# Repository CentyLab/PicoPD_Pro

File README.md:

# PicoPD Pro
Pico PD Pro is a development board for USB Power Delivery development with Raspberry Pi Pico footprint. The board can help you negotiate voltage from USB PD 3.1 with PPS (programable power supply) and AVS (Adjustable Voltage Supply) up to 5A of current at 30V max. The board feature input current/voltage/temperture reading as well as power switch to cut of the current to external devices. The 30V voltage limit is the max input voltage of the AP33772S IC.

# Quick links
[AP33772S Cpp Library](https://github.com/CentyLab/AP33772S-Cpp)

[AP33772S CircuitPython Library](https://github.com/hansendc/CircuitPython_AP33772s/) -> Big thanks to [@hansendc](https://github.com/hansendc)

[PicoPD Pro Pinout](#picopd-pro-pinout)

[Setup for AP33772S objects](#setup-for-AP33772S-objects)

[Basic AP33772S functions](#basic-ap33772S-functions)

[Important note](#important-note)

[Arduino IDE setup](#arduino-ide-setup)

[VSCode PlatformIO setup](#vscode-platformio-setup)

[Enable Serial print for debugging](#enable-serial-debug)

# PicoPD Pro Pinout

# Setup for AP33772S objects
To use AP33772 IC with the library, first you need to create a `usbpd` object. Then set up your I2C pins and start collecting the power profiles from your charger. Ensure your delay after `Wire.begin()` is more than 500ms for stable PDOs request. Enable pin 23 to allow VBUS pass-through.
```
AP33772S usbpd; // Automatically wire to Wire0

void setup()
{
  Wire.setSDA(0); // Set the correct SDA0 pin
  Wire.setSCL(1); // Set the correct SCL0 pin
  Wire.begin();
  Serial.begin(115200);
  delay(1000); 		// Delay is needed for the IC to obtain PDOs
  usbpd.begin(); 	// Start pulling the PDOs from power supply

  pinMode(25, OUTPUT); // Built in LED

  usbpd.printPDO(); //Print out PDO to Serial port
  usbpd.setOutput(0); // Turn off output switch
}
```

# Basic AP33772S functions
Common functions are:
```
displayProfiles(); //Print out PDOs in Serial
mapPPSAVSInfo();
setFixPDO(int pdoIndex, int max_current);
setPPSPDO(int pdoIndex, int target_voltage, int max_current);
setAVSPDO(int pdoIndex, int target_voltage, int max_current);
setOutput(uint8_t flag);

readVoltage();      //Return voltage in mV
readCurrent();      //Return current in mA      
readTemp();         //Return temperature in C                          
```

# Important note

Calling `usbpd.displayProfiles()` without `Serial.begin()` can soft-brick your PicoPD. Causing the IC to be non-recognizable by your computer. You will have to use PicoProbe to reflash the chip. Check out @Patronics [PicoProbePCB](https://github.com/Patronics/PicoProbePCB) if you would like to make a stable fixture for firmware debugging.

If you want to use PicoPD Pro as an AP33772S evalulation board with your own micro-controller, flash the board with **AP33772S_Eval.uf2** using the drag and drop method. This firmware will config GP0 and GP1 as INPUT to prevent I2C interferance with your own add on micro-controller like ESP32 or STM32.

# Enable Serial Debug

To enable Serial debug, there are 2 main methods:

**Using USB-C Power/Data splitter (easiest):** Use a USB-C Splitter that separates the USB 2.0 signal into another USB-C port. You only need USB 2.0 FullSpeed (12Mbps) for the job, but never hurts to get extra speed if needed later. 

* [USB-C Power/Data Splitter](https://lectronz.com/products/usb-c-splitter) (USB-HighSpeed)
* [USB-C PD Power Splitter](https://www.tindie.com/products/essenceeng/usb-c-pd-power-splitter/) (USB-HighSpeed)

**Using UART communication**: Make sure you are not using GP0 and GP1 as they are reserved for I2C0 channel for AP33772 IC. Check out Youtube tutorial: [Talk to Your Pico Over Serial](https://www.youtube.com/watch?v=pbWhoJdYA1s)

# Arduino IDE setup
Open Arduino IDE, select File -> Preference

Copy this line below and place in "Aditional Boards Manager URLs" -> OK. This will allow you to pull the Earlephilhower Pico core that work with the AP33772 library.

```
https://github.com/earlephilhower/arduino-pico/releases/download/global/package_rp2040_index.json
```

From Board Manager, search for "Pico" and install the "Raspberry Pi Pico/RP2040" core by Earlephilhower

Now from Tool -> Board -> Raspberry Pi Pico/RP2040 -> Raspberry Pi Pico

Now download the latest AP33772 library as a Zip file

```
https://github.com/CentyLab/AP33772S-Cpp
```

Import the AP33772S library into your Arduino IDE. Sketch -> Include library -> Add .ZIP Library ...

Now you start using the Example code in File -> Examples -> AP33772-Cpp-main. The example is ready to compile and flash on to your PicoPD.

Now you can plug in your USB-C cable with Power Delivery 2.0/3.0/3.1. If you also like to have serial print out, check out [Enable Serial print for debugging](#enable-serial-debug).

# VSCode PlatformIO setup
After [VSCode](https://code.visualstudio.com/) installation, you will need to install PlatformIO extension.

Now create a new PlatformIO project
+ Name:WhatEverYouWantToCallit
+ Board: Pico (RasberryPi)
+ Framework: Arduino (default)

Click "Finish"

In your new project, copy this and replace everything in platformio.ini. This is how you ask PlatformIO to compile using Earlephilhower Pico core, and enable upload via USB.

```
[env:pico]
platform = https://github.com/maxgerhardt/platform-raspberrypi.git
board = pico
framework = arduino
board_build.core = earlephilhower

;; If directly upload from PC
upload_protocol = picotool
```

Now download the latest AP33772 library as a Zip file. Unzip and place the folder in `lib`

```
https://github.com/CentyLab/AP33772S-Cpp
```

Your lib folder should look like this

To try out example code, you copy the content inside `lib/Compiled for PicoPD/PPSCycling/PPSCycling.ino`, And replace everything in your `src/main.cpp`

Now you can plug the PicoPD to your computer via USB-C and hit the upload button. After this, you will have to connect a charger to PicoPD to see the voltage cycling example. If you also like to have serial print out, check out [Enable Serial print for debugging](#enable-serial-debug).

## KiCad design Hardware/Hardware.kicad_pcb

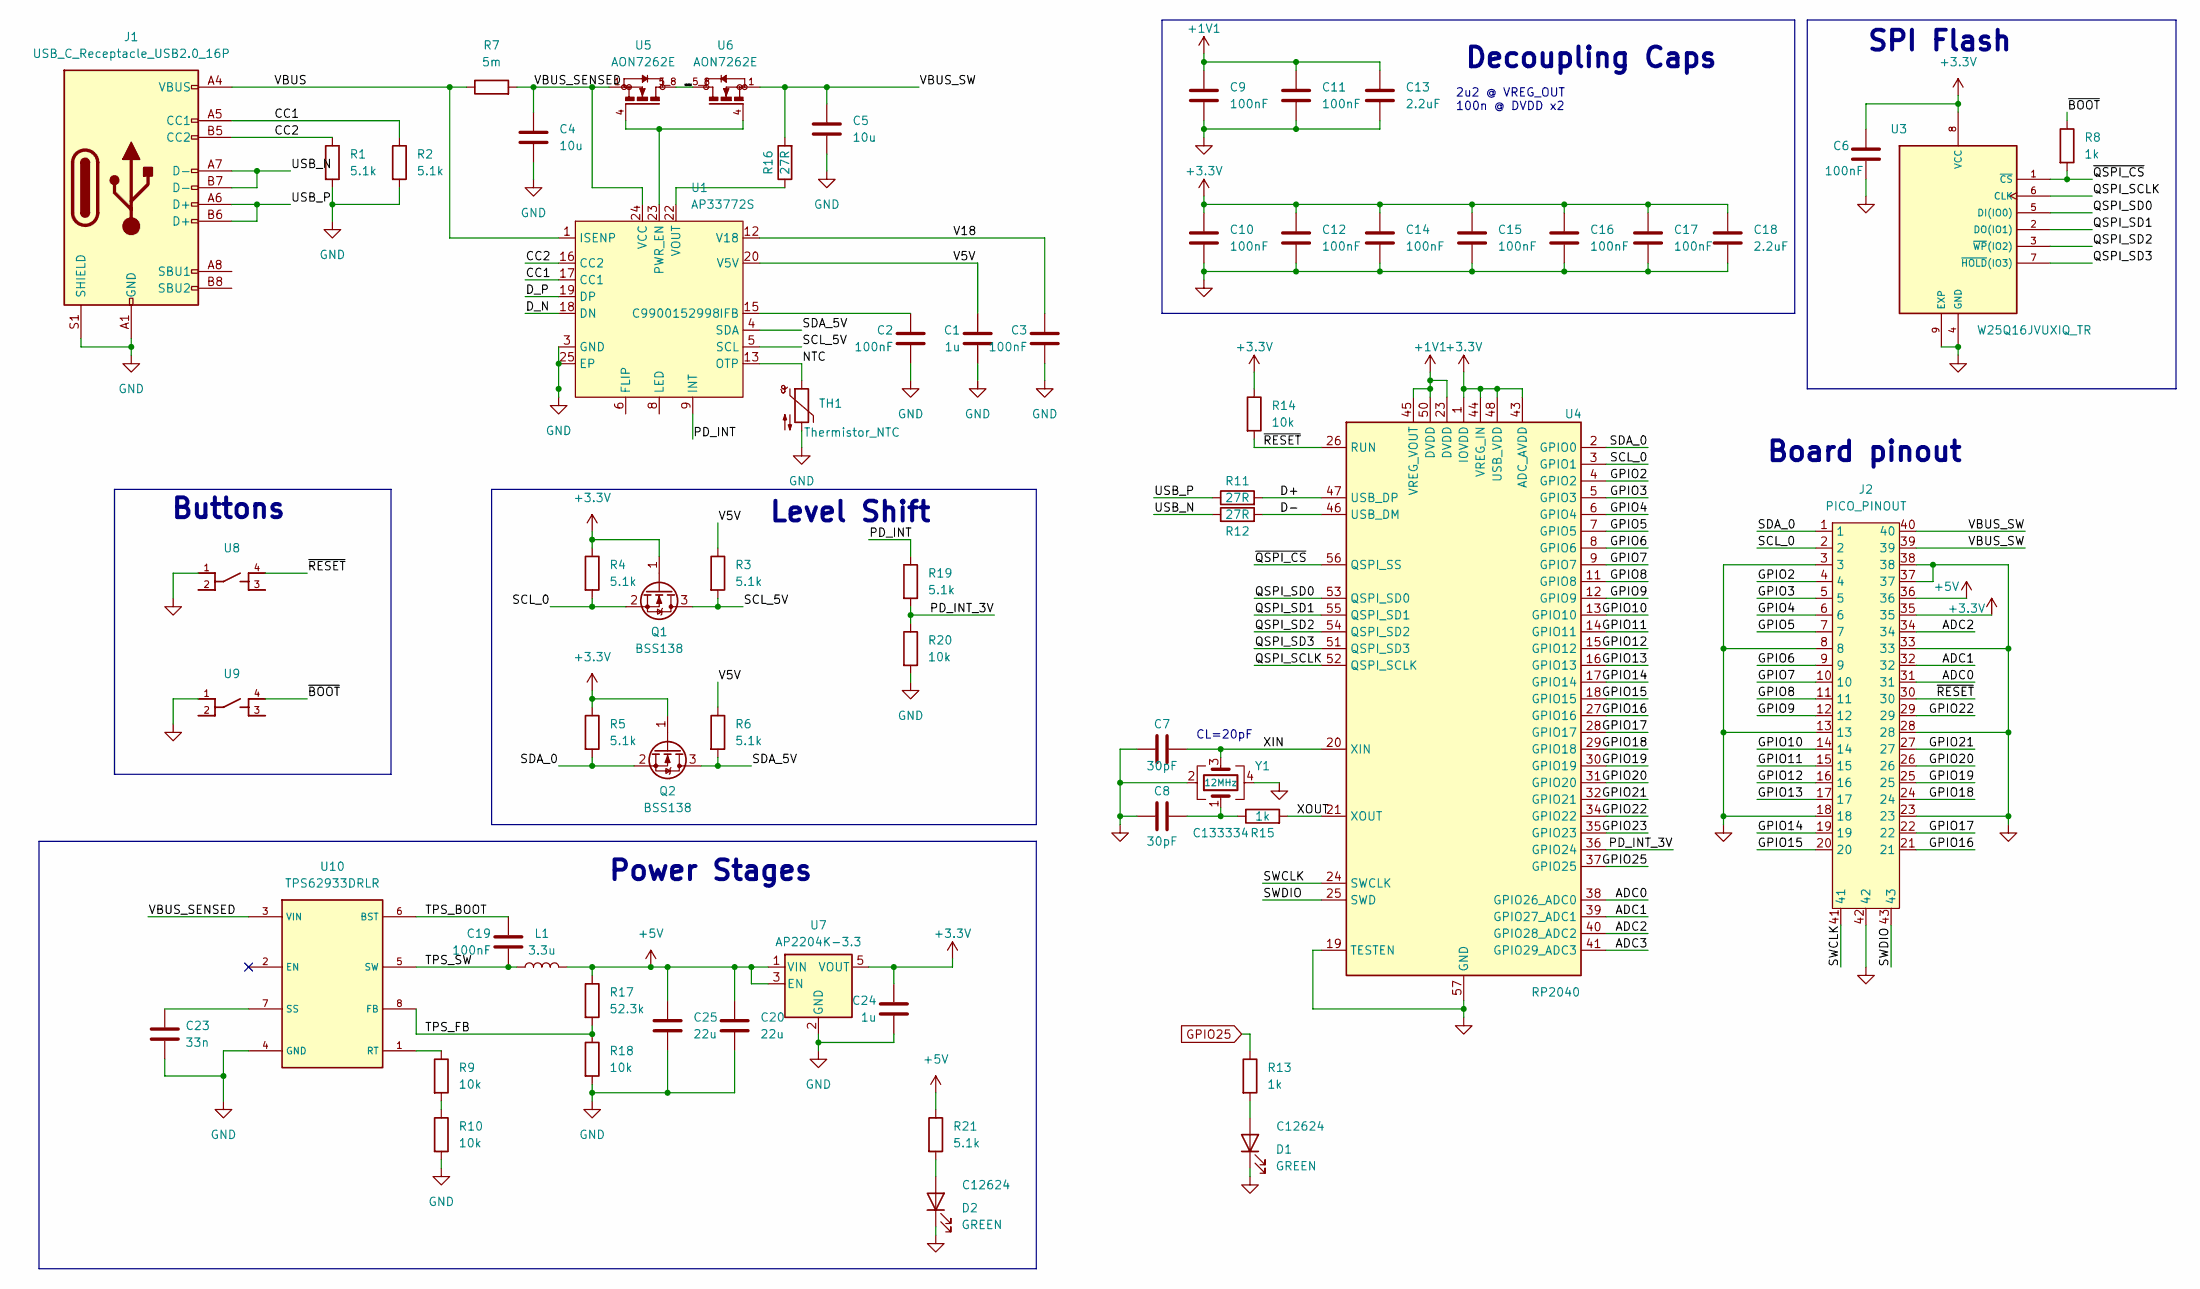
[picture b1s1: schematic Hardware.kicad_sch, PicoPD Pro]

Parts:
C1, C24: 1u; C_0603_1608Metric; LCSC C15849
C2, C3, C6, C9, C10, C11, C12, C14, C15, C16, C17, C19: 100nF; C_0402_1005Metric; LCSC C1525
C4, C5: 10u; C_1206_3216Metric; LCSC C513774
C7, C8: 30pF; C_0402_1005Metric; LCSC C1570
C13, C18: 2.2uF; C_0402_1005Metric; LCSC C12530
C20, C25: 22u; C_0805_2012Metric; LCSC C45783
C23: 33n; C_0603_1608Metric; LCSC C21117
D1, D2: GREEN; LED_0603_1608Metric; LCSC C12624
J1: USB_C_Receptacle_USB2.0_16P; USB_C_GSwitch; LCSC C963411
J2: PICO_PINOUT; PicoPD_Pinout
L1: 3.3u; L_Wuerth_MAPI-4020; LCSC C5349667
Q1, Q2: BSS138; SOT-323_SC-70; LCSC C383201
R1, R2, R3, R4, R5, R6, R19, R21: 5.1k; R_0402_1005Metric; LCSC C25905
R7: 5m; R_0805_2012Metric; Part # PA0805FRE470R005L; LCSC C728267
R8, R13, R15: 1k; R_0402_1005Metric; LCSC C11702
R9, R10, R14, R18, R20: 10k; R_0402_1005Metric; LCSC C25744
R11, R12, R16: 27R; R_0402_1005Metric; LCSC C138021
R17: 52.3k; R_0402_1005Metric; LCSC C103091
TH1: Thermistor_NTC; R_0402_1005Metric; LCSC C77131
U1: AP33772S; QFN-24-1EP_4x4mm_P0.5mm_EP2.6x2.6mm; LCSC C9900152998
U3: W25Q16JVUXIQ_TR; 8-USON; PARTREV H; LCSC C2843335
U4: RP2040; QFN-56-1EP_7x7mm_P0.4mm_EP3.2x3.2mm; LCSC C2040
U5, U6: AON7262E; DFN-8(3.3x3.3); LCSC C176755
U7: AP2204K-3.3; SOT-23-5; JLCPCB Rotation Offset 0
U8, U9: Button_3.2x2.5; LCSC C221896
U10: TPS62933DRLR; SOT583; LCSC C3200405
Y1: 12MHz; Crystal_SMD_3225-4Pin_3.2x2.5mm; LCSC C133334

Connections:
+1V1: C9.1, C11.1, C13.1, U4.23 (DVDD), U4.45 (VREG_VOUT), U4.50 (DVDD)
+3.3V: C6.1, C10.1, C12.1, C14.1, C15.1, C16.1, C17.1, C18.1, C24.1, J2.35, Q1.1 (G), Q2.1 (G), R4.1, R5.1, R14.1, U3.8 (VCC), U4.1 (IOVDD), U4.10 (IOVDD), U4.22 (IOVDD), U4.33 (IOVDD), U4.42 (IOVDD), U4.43 (ADC_AVDD), U4.44 (VREG_IN), U4.48 (USB_VDD), U4.49 (IOVDD), U7.5 (VOUT)
+5V: C20.1, C25.1, J2.36, L1.2, R17.1, R21.1, U7.1 (VIN), U7.3 (EN)
/ADC0: J2.31, U4.38 (GPIO26_ADC0)
/ADC1: J2.32, U4.39 (GPIO27_ADC1)
/ADC2: J2.34, U4.40 (GPIO28_ADC2)
/ADC3: U4.41 (GPIO29_ADC3)
/CC1: J1.A5 (CC1), R2.1, U1.17 (CC1)
/CC2: J1.B5 (CC2), R1.1, U1.16 (CC2)
/D+: R11.2, U4.47 (USB_DP)
/D-: R12.2, U4.46 (USB_DM)
/D_N: U1.18 (DN)
/D_P: U1.19 (DP)
/GPIO2: J2.4, U4.4 (GPIO2)
/GPIO3: J2.5, U4.5 (GPIO3)
/GPIO4: J2.6, U4.6 (GPIO4)
/GPIO5: J2.7, U4.7 (GPIO5)
/GPIO6: J2.9, U4.8 (GPIO6)
/GPIO7: J2.10, U4.9 (GPIO7)
/GPIO8: J2.11, U4.11 (GPIO8)
/GPIO9: J2.12, U4.12 (GPIO9)
/GPIO10: J2.14, U4.13 (GPIO10)
/GPIO11: J2.15, U4.14 (GPIO11)
/GPIO12: J2.16, U4.15 (GPIO12)
/GPIO13: J2.17, U4.16 (GPIO13)
/GPIO14: J2.19, U4.17 (GPIO14)
/GPIO15: J2.20, U4.18 (GPIO15)
/GPIO16: J2.21, U4.27 (GPIO16)
/GPIO17: J2.22, U4.28 (GPIO17)
/GPIO18: J2.24, U4.29 (GPIO18)
/GPIO19: J2.25, U4.30 (GPIO19)
/GPIO20: J2.26, U4.31 (GPIO20)
/GPIO21: J2.27, U4.32 (GPIO21)
/GPIO22: J2.29, U4.34 (GPIO22)
/GPIO23: U4.35 (GPIO23)
/NMOS: U5.5_8, U6.5_8
/NTC: TH1.1, U1.13 (OTP)
/PD_INT: R19.1, U1.9 (INT)
/PD_INT_3V: R19.2, R20.1, U4.36 (GPIO24)
/QSPI_SCLK: U3.6 (CLK), U4.52 (QSPI_SCLK)
/QSPI_SD0: U3.5 (DI(IO0)), U4.53 (QSPI_SD0)
/QSPI_SD1: U3.2 (DO(IO1)), U4.55 (QSPI_SD1)
/QSPI_SD2: U3.3 (~WP(IO2)), U4.54 (QSPI_SD2)
/QSPI_SD3: U3.7 (~HOLD(IO3)), U4.51 (QSPI_SD3)
/SCL_0: J2.2, Q1.2 (S), R4.2, U4.3 (GPIO1)
/SCL_5V: Q1.3 (D), R3.2, U1.5 (SCL)
/SDA_0: J2.1, Q2.2 (S), R5.2, U4.2 (GPIO0)
/SDA_5V: Q2.3 (D), R6.2, U1.4 (SDA)
/SWCLK: J2.41, U4.24 (SWCLK)
/SWDIO: J2.43, U4.25 (SWD)
/TPS_BOOT: C19.1, U10.6 (BST)
/TPS_FB: R17.2, R18.1, U10.8 (FB)
/TPS_SW: C19.2, L1.1, U10.5 (SW)
/USB_N: J1.A7 (D-), J1.B7 (D-), R12.1
/USB_P: J1.A6 (D+), J1.B6 (D+), R11.1
/V5V: C1.1, R3.1, R6.1, U1.20 (V5V)
/V18: C3.1, U1.12 (V18)
/VBUS: J1.A4 (VBUS), J1.A9 (VBUS), J1.B4 (VBUS), J1.B9 (VBUS), R7.1, U1.1 (ISENP)
/VBUS_SENSED: C4.1, R7.2, U1.24 (VCC), U5.1, U5.2, U5.3, U10.3 (VIN)
/VBUS_SW: C5.1, J2.39, J2.40, R16.2, U6.1, U6.2, U6.3
/XIN: C7.1, U4.20 (XIN), Y1.3
/XOUT: R15.2, U4.21 (XOUT)
/~BOOT: R8.1, U9.4
/~QSPI_CS: R8.2, U3.1 (~CS), U4.56 (QSPI_SS)
/~RESET: J2.30, R14.2, U4.26 (RUN), U8.4
GND: C1.2, C2.2, C3.2, C4.2, C5.2, C6.2, C7.2, C8.2, C9.2, C10.2, C11.2, C12.2, C13.2, C14.2, C15.2, C16.2, C17.2, C18.2, C20.2, C23.2, C24.2, C25.2, D1.1 (K), D2.1 (K), J1.A1 (GND), J1.A12 (GND), J1.B1 (GND), J1.B12 (GND), J1.S1 (SHIELD), J2.3, J2.8, J2.13, J2.18, J2.23, J2.28, J2.33, J2.37, J2.38, J2.42, R1.2, R2.2, R10.2, R18.2, R20.2, TH1.2, U1.2 (NC), U1.3 (GND), U1.7 (NC), U1.10 (NC), U1.11 (NC), U1.14 (NC), U1.21 (NC), U1.25 (EP), U3.4 (GND), U3.9 (EXP), U4.19 (TESTEN), U4.57 (GND), U7.2 (GND), U8.1, U9.1, U10.4 (GND), Y1.2, Y1.4
GPIO25: R13.1, U4.37 (GPIO25)
unnamed: C8.1, R15.1, Y1.1
unnamed: D1.2 (A), R13.2
unnamed: D2.2 (A), R21.2
unnamed: R9.2, R10.1
unnamed: C2.1, U1.15 (IFB)
unnamed: U1.23 (PWR_EN), U5.4, U6.4
unnamed: R16.1, U1.22 (VOUT)
unnamed: R9.1, U10.1 (RT)
unnamed: C23.1, U10.7 (SS)

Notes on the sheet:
Buttons
CL=20pF
SPI Flash
Board pinout
Power Stages
Level Shift
2u2 @ VREG_OUT 100n @ DVDD x2
Decoupling Caps

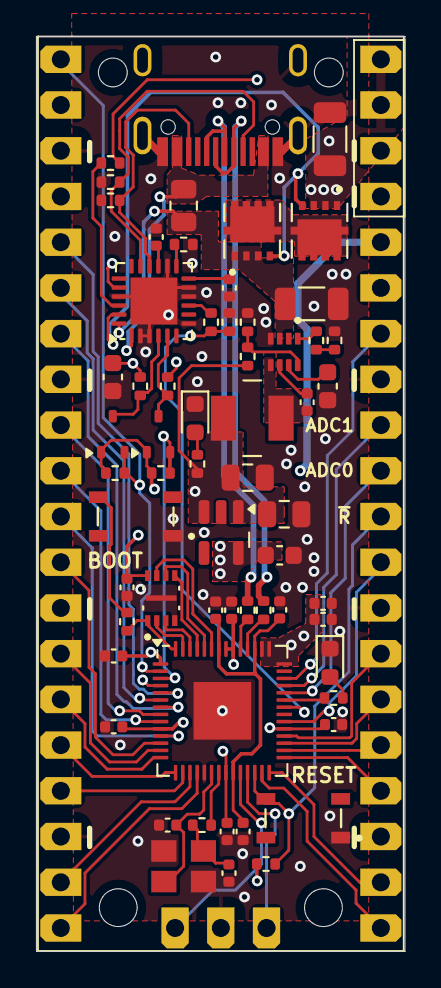
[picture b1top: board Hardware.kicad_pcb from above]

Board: 4 copper layers, 20.5 x 50.8 mm, 62 parts (0 on the bottom side), 72 nets.

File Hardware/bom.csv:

Designator,Footprint,Quantity,Value,LCSC Part #
"C1, C24",0603,2,1u,C15849
"C10, C11, C12, C14, C15, C16, C17, C19, C2, C3, C6, C9",0402,12,100nF,C1525
"C13, C18",0402,2,2.2uF,C12530
"C20, C25",0805,2,22u,C45783
C23,0603,1,33n,C21117 
"C4, C5",1206,2,10u,C513774
"C7, C8",0402,2,30pF,C1570
"D1, D2",0603,2,GREEN,C12624
J1,USB_C_GSwitch,1,USB_C_Receptacle_USB2.0_16P,C963411
L1,L_Wuerth_MAPI-4020,1,3.3u,C5349667
"Q1, Q2",SOT-323_SC-70,2,BSS138,C383201
"R1, R19, R2, R21, R3, R4, R5, R6",0402,8,5.1k,C25905
"R10, R14, R18, R20, R9",0402,5,10k,C25744
"R11, R12, R16",0402,3,27R,C138021
"R13, R15, R8",0402,3,1k,C11702
R17,0402,1,52.3k, C103091
R7,0805,1,5m, C728267
TH1,0402,1,Thermistor_NTC,C77131
U1,QFN-24-1EP_4x4mm_P0.5mm_EP2.6x2.6mm,1,AP33772S,C9900152998
U10,SOT583,1,TPS62933DRLR,C3200405
U3,8-USON,1,W25Q16JVUXIQ_TR,C2843335
U4,QFN-56-1EP_7x7mm_P0.4mm_EP3.2x3.2mm,1,RP2040,C2040
"U5, U6",DFN-8(3.3x3.3),2,AON7262E,C176755
U7,SOT-23-5,1,AP2204K-3.3,C112032
"U8, U9",Button_3.2x2.5,2,~,C221896
Y1,Crystal_SMD_3225-4Pin_3.2x2.5mm,1,12MHz,C133334

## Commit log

2024-12-12 Add blank code for AP33772S eval mode
2024-12-22 Update BOM
2025-01-24 Rename folders and add CircuitPython Support
2025-01-24 Readd CPP firmware
2025-02-10 Add LDO alternative
2025-03-31 Changed VBus_SW and GND pins to solid copper
2025-04-02 reduced soild copper pins to 37-40 and added high power silkscreen markings to 37-40
2025-07-27 Update pinout
